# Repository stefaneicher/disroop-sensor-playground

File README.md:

# disroop-sensor-playground

**Ein kleiner Sensor-Würfel wird zum Gamecontroller:** Der Nordic Thingy:52 schickt seine Sensordaten per Bluetooth live an ein Dashboard. Er dient als Tennisschläger, und auf der Lauberhorn-Abfahrt lenkst du damit den Skifahrer.

> **Was ist der Thingy:52?** Ein etwa 6 × 6 cm grosses Entwicklungsboard von Nordic Semiconductor im Gummigehäuse. Es enthält einen nRF52832-Chip mit Bluetooth LE und NFC, eine Bewegungseinheit (Beschleunigung, Gyro, Kompass), Temperatur-, Feuchte- und Luftdrucksensor, Gas- und Farbsensor, Mikrofon, Lautsprecher, eine RGB-LED und einen Taster. Foto und Datenblatt: [Nordic Thingy:52 – Produktseite](https://www.nordicsemi.com/Products/Development-hardware/Nordic-Thingy-52), [Werksfirmware auf GitHub](https://github.com/NordicSemiconductor/Nordic-Thingy52-FW).

Das Projekt hat drei Teile. Der Thingy läuft dabei immer mit der **Werksfirmware**, Flashen ist nicht nötig.

### 1. Sensorübersicht mit Verwendungszwecken

Alle Sensorwerte laufen per Bluetooth LE live ins Terminal, in ein Web-Dashboard und in eine Android-App. Zu jedem Sensor erklärt das Dashboard, wofür man ihn braucht (ⓘ). Der Thingy spielt dazu „Highway to Hell“, die LED blinkt mit.

*Web-Dashboard im Simulator-Modus (`thingy.exe --sim`). Mobile-Ansicht: [docs/img/dashboard-mobile.png](docs/img/dashboard-mobile.png)*

*Android-App im Simulator-Modus. Die Bilder erzeugt `./project android screenshots`.*

### 2. Tennis

*Tennis im Browser, der Thingy ist der Schläger: `thingy.exe tennis` (live) oder `thingy.exe tennis --sim`. In der Android-App über „🎾 Tennis“. Mehr in [docs/TENNIS.md](docs/TENNIS.md).*

### 3. Skiabfahrt

*Abfahrt auf Lauberhorn und Streif, der Thingy ist der Lenker: kippen = lenken, Nase runter = Hocke, Ruck = Sprung. http://127.0.0.1:8052/ski oder in der Android-App über „⛷ Ski“. Mehr in [docs/SKI.md](docs/SKI.md).*

> **Thingy:52-Pfad: keine Firmware, kein Flashen, kein Debugger.** Für den Thingy wird keine eigene Firmware gebaut. Der Thingy läuft unverändert mit der Nordic-Werksfirmware (v2.x). Bridge und Android-App sind **BLE-Clients**:
> - **Empfangen:** Sie abonnieren die GATT-Notifications des Thingy (Sensordaten) und dekodieren sie.
> - **Senden:** Sie schreiben Befehle in GATT-Characteristics: Ton für das Lied, LED-Farbe, Sensor-Intervalle, NFC-Inhalt.
>
> Das hat Grenzen: Es geht nur, was die Werksfirmware anbietet. So ist z. B. die Mikrofon-Abtastrate fest auf 16 kHz. Deshalb ist die Lautstärkemessung standardmässig aus, sie würde die BLE-Verbindung überlasten.
>
> ```
> Thingy:52 (Werks-FW) ──BLE──▶ thingy.exe (Windows) ──▶ Terminal + Web-Dashboard :8052
>                      ──BLE──▶ Android-App ch.disroop.sensorplayground (direkt, Start per NFC)
> ```

Das separate Motion-One-Teilprojekt enthält dagegen eigene Firmwareentwürfe.

## Features

- **`thingy.exe`** (Go, Windows): verbindet sich per BLE mit dem Thingy und zeigt alle Werte live im Terminal:
  - Beschleunigung, Gyro, Kompass, Kurs, Euler-Winkel, Lage, Tippen, Schritte
  - Temperatur, Feuchte, Luftdruck, eCO₂/TVOC, Farbe
  - Mikrofonpegel, Taster, Akku, RSSI
- **Web-Dashboard** auf http://localhost:8052. Es ist in die exe eingebettet und bekommt die Daten live per Server-Sent Events. Es zeigt Charts, 3D-Lage und Kompass, und du kannst damit das Lied und die LED steuern.
- **Lied:** „Highway to Hell“ (Refrain, 24 Noten) über den Thingy-Lautsprecher. Die LED-Farbe folgt der Tonhöhe. Starten und stoppen geht per Taster am Thingy, im Dashboard oder in der App.
- **NFC:** `thingy.exe nfc` schreibt einen Android Application Record auf den NFC-Tag des Thingy. Hältst du das Handy an den Thingy, öffnet sich die App.
- **Android-App** `ch.disroop.sensorplayground`: verbindet sich direkt per BLE und zeigt dieselben Werte. Sie hat einen eingebauten Simulator.
- **Tennis** (`tennis/`, eigenes Programm): Tennis-Spiel mit three.js, der Thingy ist der Schläger. Schwung = Schlag, Neigen = laufen. Die Bridge liefert die Bewegung mit 100 Hz per WebSocket und spielt das Spiel unter `/tennis/` aus. Ohne Thingy mit Tastatur oder im Simulator spielbar. Dazu **Ski** (`tennis/src/ski/`): Lauberhorn und Streif in 3D, siehe [docs/SKI.md](docs/SKI.md).
- **Simulator** (`--sim`) für Demos, Tests und CI ohne Hardware.
- **Alles im Docker-Devcontainer:** Lokal wird ausser Docker nichts installiert.

## Quickstart

**Voraussetzungen**
- Windows 11 mit WSL2 (Ubuntu) und Docker in WSL
- Bluetooth-LE-Adapter unter Windows
- Thingy:52 mit Werksfirmware, geladen. Zum Aufwecken den Knopf drücken.

**Im Repo-Ordner unter WSL:**

```bash
./project image          # Devcontainer-Image bauen (einmalig, dauert einige Minuten)
./project build          # build/thingy.exe, build/thingy-linux, build/disroop-sensor-playground-debug.apk
./project bridge run     # thingy.exe auf Windows starten: Terminal-Live-Ansicht + Web-GUI
```

Dann im Browser http://localhost:8052 öffnen. `Strg+C` beendet die exe.

**Ohne Hardware:** `./project bridge run --sim` startet die exe mit dem Simulator.

**Tennis:** `./project play` (echter Thingy) oder `./project play --sim` baut alles, startet `thingy.exe tennis` und öffnet http://127.0.0.1:8052/tennis/. Mit dem Invoke-CLI: `./t tennis.play [--sim]`. Anleitung: [docs/TENNIS.md](docs/TENNIS.md).

> Die exe läuft über WSL-Interop **unter Windows**, weil WSL kein Bluetooth hat. Der Port lauscht nur auf `127.0.0.1` von Windows. Aus WSL brauchst du deshalb `curl.exe` statt `curl`, siehe [Troubleshooting](docs/TROUBLESHOOTING.md).

## Android-App installieren

1. APK bauen mit `./project android build`. Das ergibt `build/disroop-sensor-playground-debug.apk`. Ein GitHub-Release mit fertiger APK ist geplant, siehe [Releases](https://github.com/stefaneicher/disroop-sensor-playground/releases).
2. Installieren:
   - **Sideload:** APK aufs Handy kopieren, öffnen und „Unbekannte Apps installieren“ erlauben.
   - **adb (Windows):** `adb install -r build\disroop-sensor-playground-debug.apk`
3. Beim ersten Start die Berechtigung „Geräte in der Nähe“ (Bluetooth) erteilen.

Die APK ist mit einem öffentlich eingecheckten Demo-Schlüssel signiert. Neuinstallationen über lokale und CI-Builds hinweg funktionieren deshalb. Für den produktiven Einsatz ist sie nicht gedacht.

## NFC: Handy an den Thingy halten

```bash
./project bridge nfc             # Backup nach build/nfc-backup.hex, dann AAR "ch.disroop.sensorplayground" schreiben
./project bridge nfc --restore   # Original-Inhalt (Nordic-App) aus dem Backup zurückschreiben
```

Der Thingy nimmt nur **eine** BLE-Verbindung an. Während `nfc` läuft, müssen `thingy.exe` und die App getrennt sein.

## Projektstruktur

```
project                 CLI: ./project <befehl>, ruft scripts/<bereich>.sh auf
scripts/                bridge.sh, web.sh, tennis.sh, android.sh (Builds und Tests im Devcontainer)
.devcontainer/          Toolchain-Image (Go, Node, JDK 21, Android SDK, Chromium)
bridge/                 Go: thingy.exe (BLE, Decoder, Telemetrie, TUI, HTTP/SSE, Lied, NFC)
bridge/web/             Web-Dashboard (ES-Module ohne Build-Step), Tests, Mock-Server
tennis/                 Tennis: eigenes Spiel (TypeScript + three.js, kein Bundler), von der exe unter /tennis/ ausgeliefert
android/                Android-App (Kotlin, Compose) + reines Kotlin-Modul :protocol
shared/                 chorus.json (Lied), telemetry.example.json (Beispiel-Snapshot)
docs/                   Protokoll-Vertrag, Schema, Architektur, Anleitungen
devices/motion-one/     Eigener Controller „Disroop Motion One“: digitaler Entwurf, nicht hardwarevalidiert
build/                  Build-Ausgaben (nicht im Git)
```

## Motion One: aktueller Stand und Archiv

PCB/Firmware liegen auf r4; die Mechanikquellen enthalten r5-Änderungen, aber noch
keine gespeicherten r5-Prüfergebnisse. Verbindlich ist der
[Projektstand](devices/motion-one/management/PROJECT_STATE.md), visuell aufbereitet im
[aktuellen Überblick](devices/motion-one/media/presentation/index.html).
Die [V1-Baseline](devices/motion-one/releases/V1_BASELINE/VERIFIKATIONSMATRIX.md) und
der r3-Zwischenbericht bleiben historische Nachweise, keine aktuelle Fertigungsfreigabe.

Das [Dateiaudit](docs/DATEI_AUDIT.html) bewertet Projektpfade, Referenzhinweise und
bytegleiche Duplikate. Erneut erzeugen: `node scripts/audit-files.mjs`.
Fehlende Textreferenzen allein rechtfertigen keine Löschung.

Nach Veröffentlichung auf `main` direkt als HTML:
[Projektüberblick](https://raw.githack.com/stefaneicher/disroop-sensor-playground/main/devices/motion-one/media/presentation/index.html)
und [Dateiaudit](https://raw.githack.com/stefaneicher/disroop-sensor-playground/main/docs/DATEI_AUDIT.html).

## Dokumentation

Die Übersicht findest du in [docs/index.md](docs/index.md):

- [Architektur](docs/ARCHITECTURE.md)
- [Bedienung](docs/USAGE.md)
- [Entwicklung](docs/DEVELOPMENT.md)
- [Troubleshooting](docs/TROUBLESHOOTING.md)
- [Protokoll-Vertrag](docs/protocol.md)
- [Tennis](docs/TENNIS.md)
- READMEs der Bereiche: [bridge](bridge/README.md), [web](bridge/web/README.md), [tennis](tennis/README.md), [android](android/README.md)

## Lizenz

© 2026 Stefan Eicher. Alle Rechte vorbehalten, siehe [LICENSE](LICENSE). „Highway to Hell“ ist hier nur als grobe Tonfolge des Refrains enthalten (`shared/chorus.json`).

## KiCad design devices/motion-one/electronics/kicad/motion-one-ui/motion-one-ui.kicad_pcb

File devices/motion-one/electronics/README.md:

# Elektronik und PCB

Hier liegen Schaltplan, KiCad-Layout, elektrische Simulationen, Baugruppenexport und Firmware-Pinout.

## Stand

Standabgleich 2026-11-13: PCB r4 mit integriertem hierarchischem Schaltplan r4-C.
Die gespeicherten Integrationsbelege vom 2026-11-09 melden Netzlisten MATCH, ERC
ohne Fehler und keine offenen Verbindungen; Hauptplatine mit zwei DRC-Warnungen,
UI ohne DRC-Warnungen [QUELLE:
`exports/pruefbelege_schaltplan_r4/hierarchy-integration.json`]. Die UI-Platine ist
optional und nicht Teil des Geräts/Gehäuses r4. Gesamtstatus **PARTIAL**;
verbindlich ist [PROJECT_STATE](../management/PROJECT_STATE.md).

Das V1-Board ist als 4-Lagen-KiCad-Projekt (70 × 25 × 1,0 mm) erstellt und vollständig geroutet. Der dokumentierte
Prüflauf meldet ERC: 0 Fehler und DRC: 0 Fehler/0 unverbundene Netze; zwei USB-C-Silkscreen-Warnungen sind begründet.
SPICE-Fälle für Power-Path, Einschaltstrom, Summer/Motor und Akku-Messteiler wurden simuliert.

*KiCad-Render des digitalen PCB-Entwurfs, keine gefertigte Platine. Die endgültige PCB-/Gehäuse-Abstimmung läuft noch.*

Diese Ergebnisse gelten für den prototypischen Entwurf, nicht für ein gefertigtes Board. Der PCB-/Gehäuse-Abgleich und
die finale Revision laufen; die Fertigungsdaten müssen nach Änderungen neu exportiert und geprüft werden.

## Wichtige Dateien

- `kicad/motion-one/`: `.kicad_sch`, `.kicad_pcb`, lokale Bibliotheken und STEP-Export
- `analysis/ANALYSE_V1.md`: Leistungs-, Lade-, Regler-, Toleranz- und Fertigungsanalyse
- `spice/`: ngspice-Netzlisten, Logs und Ergebnisse
- `PINOUT_V1.json`: Sollbelegung der E73-Modulsignale; wird vom Firmware-Board-Overlay übernommen
- `../manufacturing/pcba/`: Gerber, Bohrdaten, JLC-BOM/CPL und Renderings
- `../sourcing/BOM_V1.md`: Bauteile, Teilenummern und Lager-Snapshots

## Schnittstellen / offene Punkte

`../management/INTERFACES.json` ist der gemeinsame Vertrag zu Boardumriss, Bauhöhen und Positionen. Der aktuelle
PCB-Stand braucht noch die fachübergreifende Abstimmung mit der Mechanik, anschliessend neue ERC/DRC- und
Fertigungsexporte. CPL-Rotationen sind in der Bestückervorschau zu bestätigen. Finale PCBA- und Versandpreise sind
nicht belegt; ohne Bestellung/Muster bleiben elektrische Messungen NOT RUN.

## Reproduktion

Werkzeuge ausschliesslich im Hardware-Image ausführen, zum Beispiel:

```sh
./project hw run "kicad-cli version"
./project hw run "ngspice -b devices/motion-one/electronics/spice/powerpath.cir"
```

Der aktuelle Hauptschaltplan-Generator ist `../scripts/electronics/gen_mo_sch_hier.py`.
Ältere Generatoren und Migrationsskripte sind keine austauschbaren Einstiegspunkte:
Sie können ältere Stände erzeugen oder Quellen verändern. Die genauen Generator-,
ERC-, DRC- und Exportbefehle stehen in `../scripts/electronics/` und im datierten PCB-Handoff.

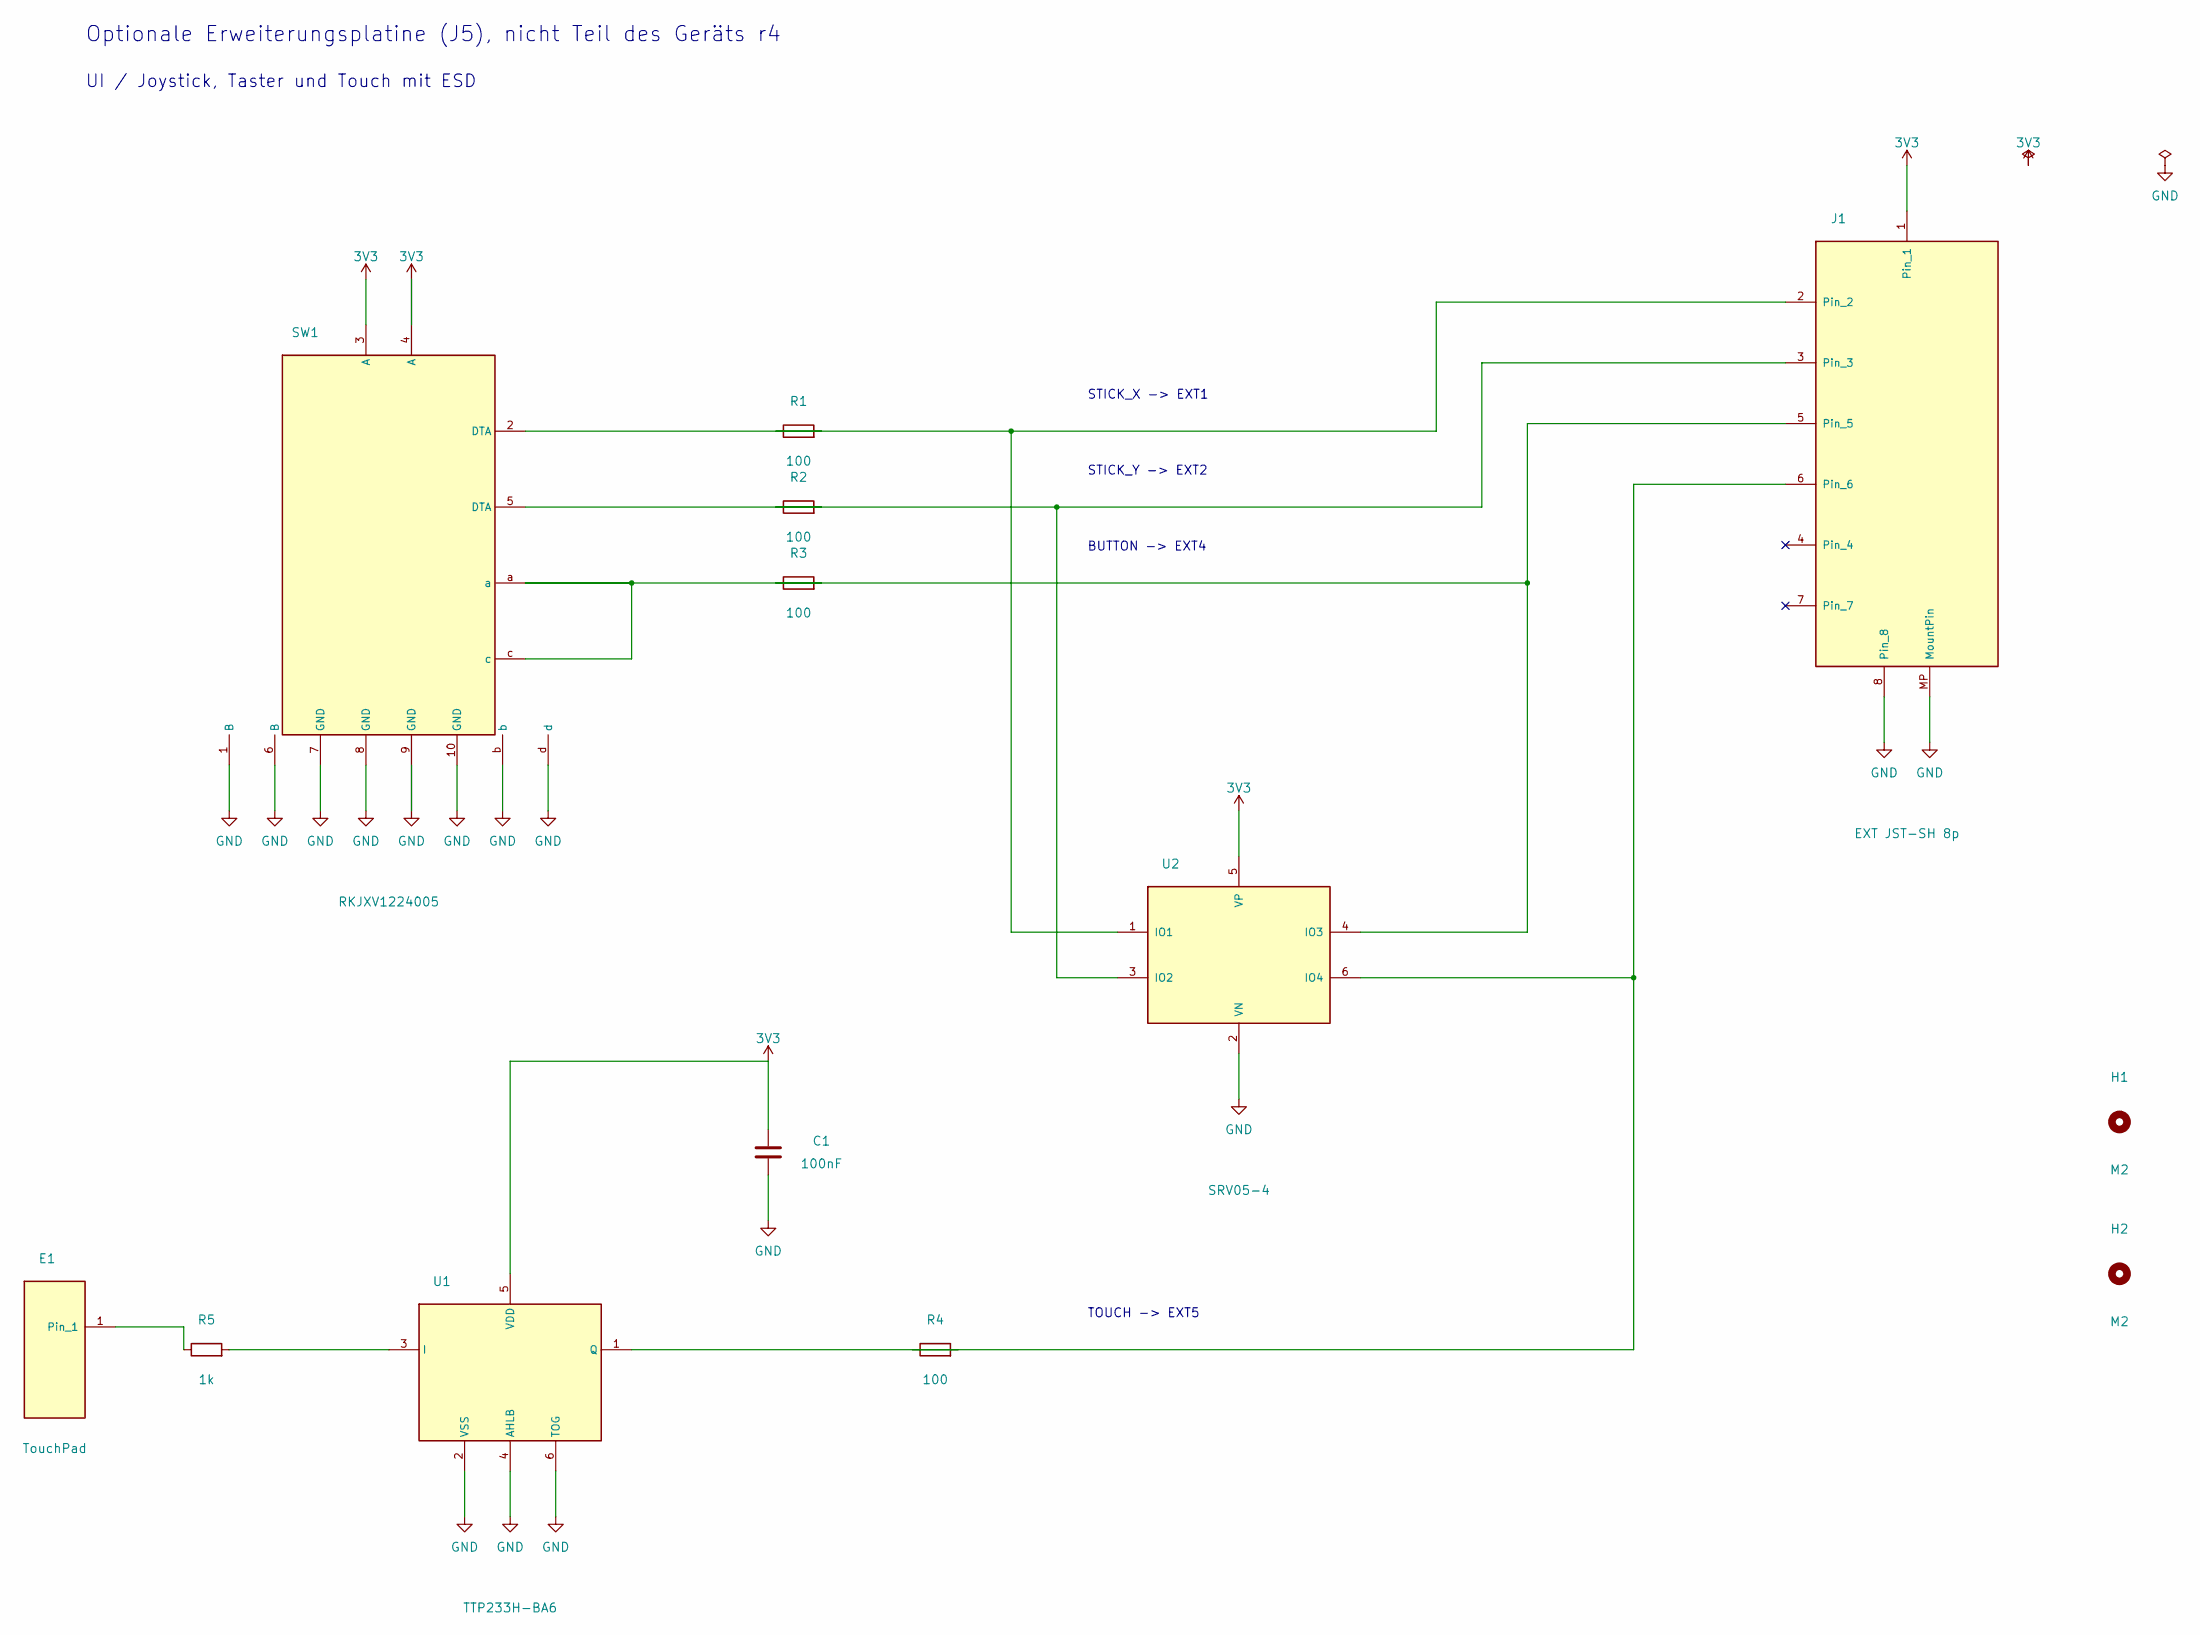
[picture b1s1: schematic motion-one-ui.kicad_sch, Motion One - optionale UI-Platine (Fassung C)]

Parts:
C1: 100nF; C_0402_1005Metric; LCSC C1525
E1: TouchPad; TouchPad_10x10
H1, H2: M2; MountingHole_2.2mm_M2
J1: EXT JST-SH 8p; JST_SH_SM08B-SRSS-TB_1x08-1MP_P1.00mm_Horizontal; LCSC C160407
R1, R2, R3, R4: 100; R_0402_1005Metric; LCSC C25076
R5: 1k; R_0402_1005Metric; LCSC C11702
SW1: RKJXV1224005; SW-TH_RKJXV1224005; MPN RKJXV1224005; LCSC Part C146170
U1: TTP233H-BA6; SOT-23-6_L2.9-W1.7-P0.95-LS2.8-BL; MPN TTP233H-BA6; LCSC Part C2890349
U2: SRV05-4; SOT-23-6; LCSC C13612

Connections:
3V3: C1.1, J1.1, SW1.3 (A), SW1.4 (A), U1.5 (VDD), U2.5 (VP)
GND: C1.2, J1.8, J1.MP (MountPin), SW1.1 (B), SW1.6 (B), SW1.7 (GND), SW1.8 (GND), SW1.9 (GND), SW1.10 (GND), SW1.b, SW1.d, U1.2 (VSS), U1.4 (AHLB), U1.6 (TOG), U2.2 (VN)
unnamed: E1.1, R5.1
unnamed: J1.2, R1.1, U2.1 (IO1)
unnamed: J1.3, R2.1, U2.3 (IO2)
unnamed: J1.5, R3.1, U2.4 (IO3)
unnamed: J1.6, R4.1, U2.6 (IO4)
unnamed: R1.2, SW1.2 (DTA)
unnamed: R2.2, SW1.5 (DTA)
unnamed: R3.2, SW1.a, SW1.c
unnamed: R5.2, U1.3 (I)
unnamed: R4.2, U1.1 (Q)

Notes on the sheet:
Optionale Erweiterungsplatine (J5), nicht Teil des Geräts r4
UI / Joystick, Taster und Touch mit ESD
STICK_X -> EXT1
STICK_Y -> EXT2
BUTTON -> EXT4
TOUCH -> EXT5

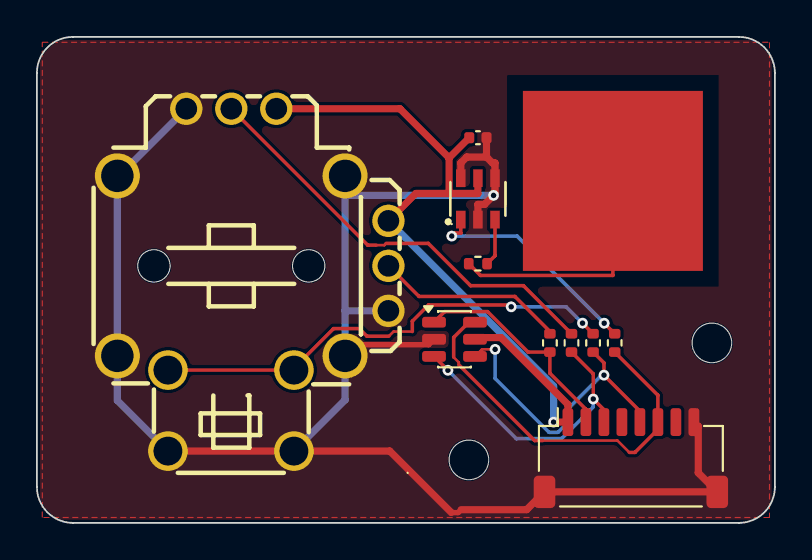
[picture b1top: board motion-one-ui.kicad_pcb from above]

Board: 2 copper layers, 41.0 x 27.0 mm, 13 parts (0 on the bottom side), 12 nets.

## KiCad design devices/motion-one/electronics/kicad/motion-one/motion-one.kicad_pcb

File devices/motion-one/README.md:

# Disroop Motion One

Ein geplanter Einhand-Motion-Controller für Tennis und Ski. Das Gerät soll das Thingy:52-BLE-Profil nachbilden, damit
Bridge, Spiele und Android-App ohne Codeänderungen funktionieren.

> **Aktueller Überblick:** [Projektstand mit Prüfgrenzen und Archiv](media/presentation/index.html).
> Verbindliche Statusquelle: [PROJECT_STATE.md](management/PROJECT_STATE.md), Abgleich vom 2026-11-13.

## Aktueller Stand

V1 ist ein **digitaler Entwicklungsstand**, noch kein fertiges oder geprüftes Produkt: PCB, Firmware und ergonomisches
Gehäuse liegen als Entwürfe vor. Die Gesamtintegration ist noch offen. Nach letztem dokumentiertem Stand wurde nichts bestellt, bezahlt,
gedruckt, geflasht oder unter Spannung gesetzt; ein neuer Durchführungsnachweis fehlt, Hardwaretests sind NOT RUN. Der detaillierte Status und die nächsten
Schritte stehen im [verbindlichen Projektstand](management/PROJECT_STATE.md).
PCB/Firmware: r4; Mechanikquellen: r5, gespeicherte Mechanik-Prüfbelege: r4.
Die V1-Baseline ist ein historischer Snapshot, keine r5-Fertigungsfreigabe.

## Themen

| Bereich | Kurzfassung | Status |
|---|---|---|
| [Elektronik / PCB](electronics/README.md) | KiCad-Board, Schaltplan, SPICE-Analyse und Pinout | Entwurf; finale Mechanik-Abstimmung offen |
| [Firmware](firmware/README.md) | Zephyr-Firmware mit Thingy-Profil, Bewegungserfassung und UF2-Programmierweg | 69 Tests ohne Fehler und Pinchecks im gespeicherten r4-Log [QUELLE: logs/fw-pinmap/unit-tests.log]; Hardware NOT RUN |
| [Mechanik](mechanics/README.md) | Parametrisches, beidhändig nutzbares Griffgehäuse, FEM und 3D-Druck | CAD und Slicer-Daten vorhanden; PCB-Abgleich offen |
| [Fertigung](manufacturing/README.md) | PCBA-Uploadpaket und Slicer-Ausgaben | Dateien vorbereitet; noch kein Auftrag oder Druck |
| [Beschaffung](sourcing/README.md) | BOM, Lagerabfragen und Bestücker-Vergleich | Momentaufnahme; finale Versand- und PCBA-Angebote offen |

## Projektdateien

- [Entwicklungsprompt](PROMPT_1_ENTWICKLUNG.md) und [Marktauftritt-Prompt](PROMPT_2_MARKTAUFTRITT.md)
- [Aktueller Projektüberblick](media/presentation/index.html)
- [Archiv: Zwischenbericht r3 vom 2026-11-08](media/presentation/ZWISCHENBERICHT_2026-11-08_r3.html)
- [Dateiaudit und Aufräumkandidaten](../../docs/DATEI_AUDIT.html)
- [Vorab-Check](PREFLIGHT.md) und [Vorbildanalyse](ANALYSE.md)
- [Hauptprotokoll](../../docs/protocol.md)

Alle Masse, Preise und Leistungswerte sind Quellenangaben, Berechnungen, Simulationen oder Annahmen; Details und
Belegpfade stehen in den jeweiligen Bereichs-README-Dateien und Handoffs. CE/RED, FCC, UN38.3, EMV und physische
Sicherheit sind nicht validiert.

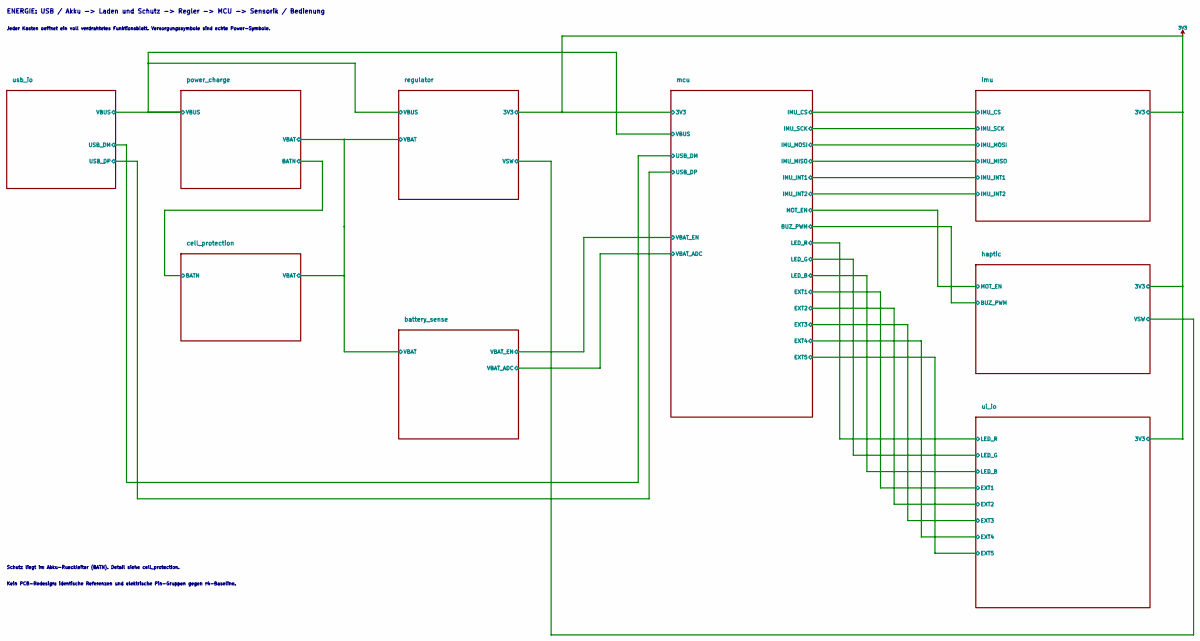
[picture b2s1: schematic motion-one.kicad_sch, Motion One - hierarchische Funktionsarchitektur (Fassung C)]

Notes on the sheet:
ENERGIE: USB / Akku -> Laden und Schutz -> Regler -> MCU -> Sensorik / Bedienung
Jeder Kasten oeffnet ein voll verdrahtetes Funktionsblatt. Versorgungssymbole sind echte Power-Symbole.
Schutz liegt im Akku-Rueckleiter (BATN). Detail siehe cell_protection.
Kein PCB-Redesign: identische Referenzen und elektrische Pin-Gruppen gegen r4-Baseline.

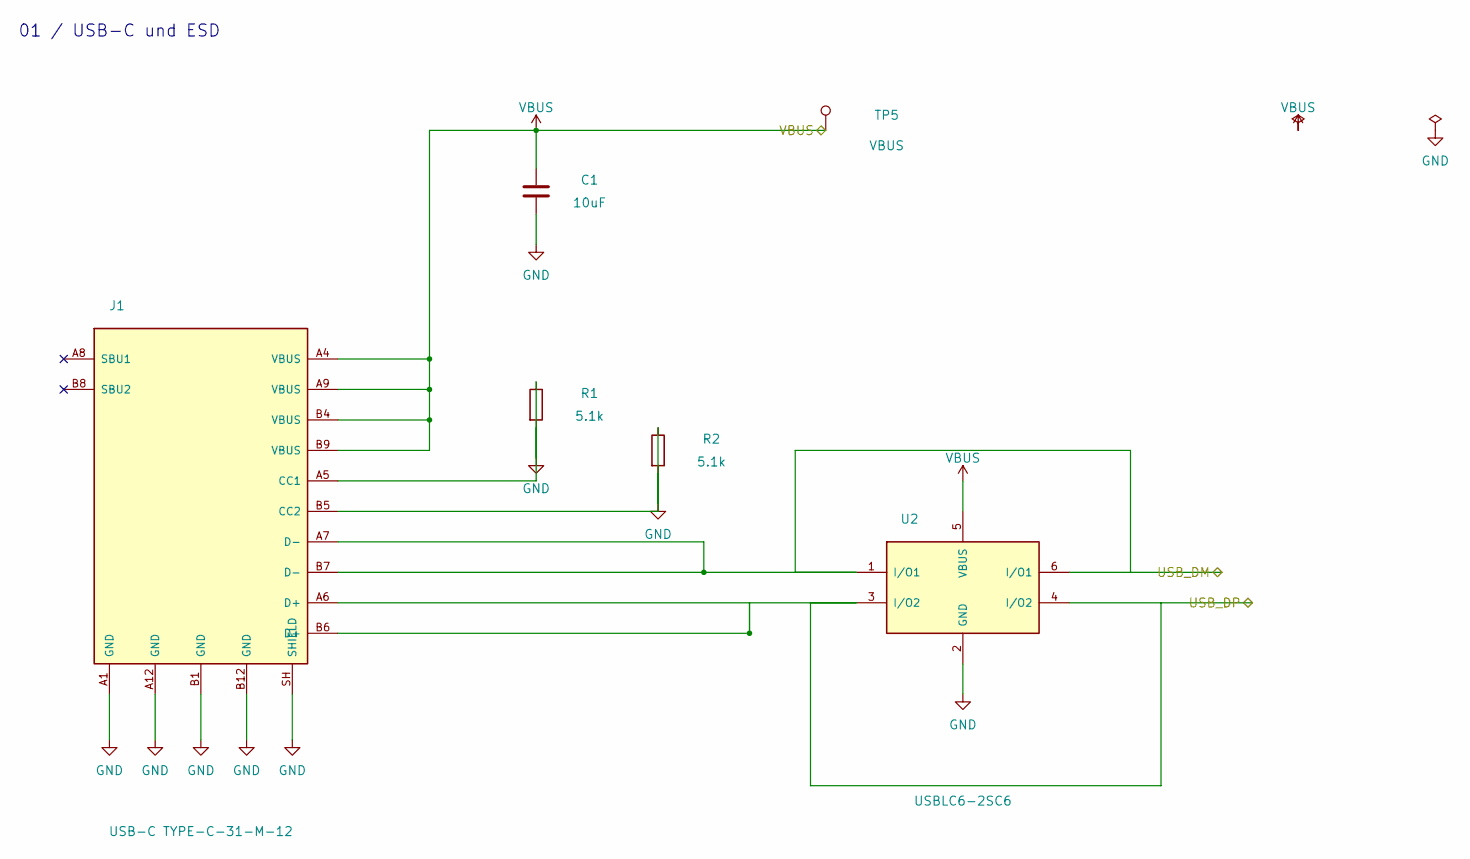
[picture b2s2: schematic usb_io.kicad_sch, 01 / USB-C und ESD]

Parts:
C1: 10uF; C_0805_2012Metric; LCSC C15850
J1: USB-C TYPE-C-31-M-12; USB_C_Receptacle_HRO_TYPE-C-31-M-12; LCSC C165948
R1, R2: 5.1k; R_0402_1005Metric; LCSC C25905
TP5: VBUS; TestPoint_Pad_D1.0mm
U2: USBLC6-2SC6; SOT-23-6; LCSC C7519

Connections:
/mcu/USB_DM: J1.A7 (D-), J1.B7 (D-), U2.1 (I/O1), U2.6 (I/O1); also elsewhere on the board
/mcu/USB_DP: J1.A6 (D+), J1.B6 (D+), U2.3 (I/O2), U2.4 (I/O2); also elsewhere on the board
VBUS: C1.1, J1.A4 (VBUS), J1.A9 (VBUS), J1.B4 (VBUS), J1.B9 (VBUS), TP5.1, U2.5 (VBUS); also elsewhere on the board

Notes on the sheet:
01 / USB-C und ESD

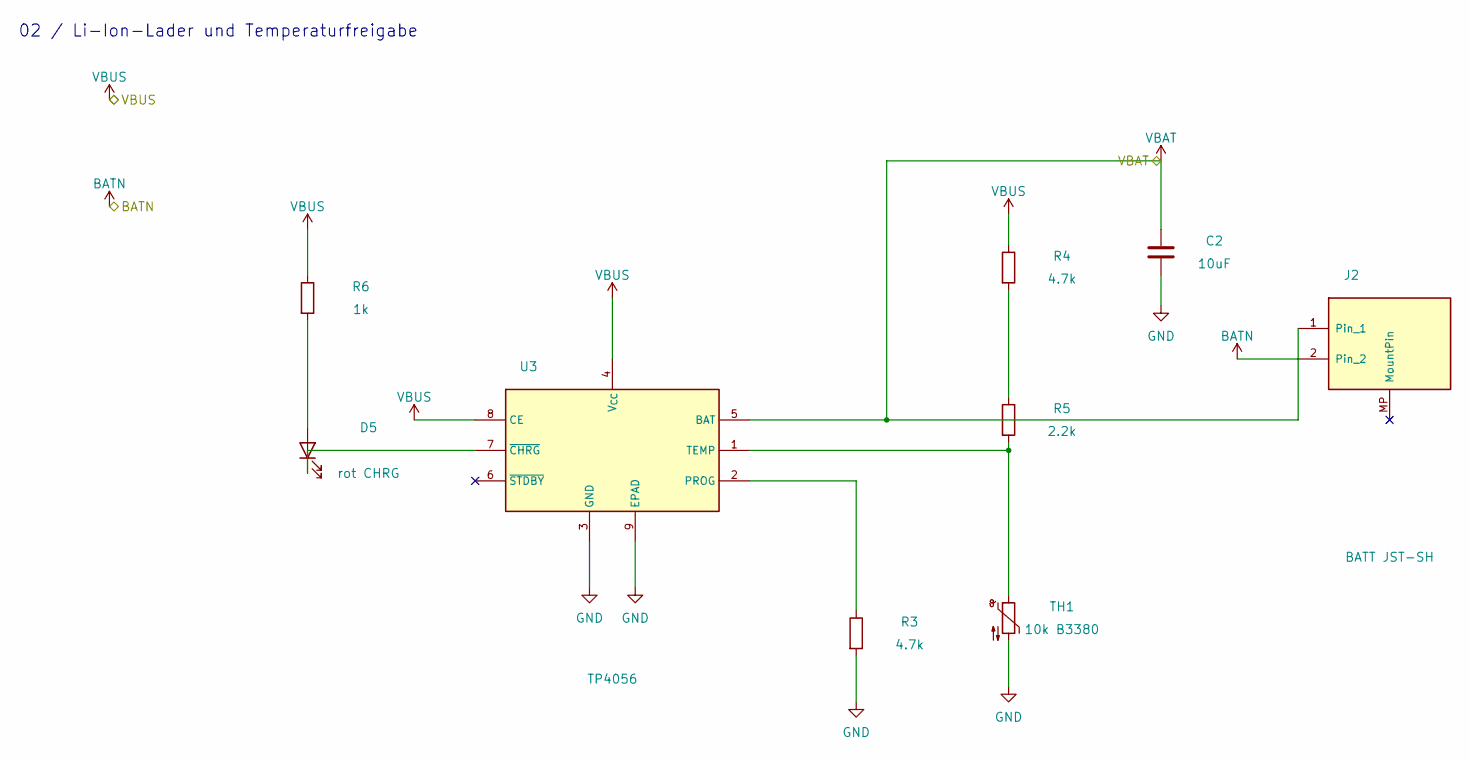
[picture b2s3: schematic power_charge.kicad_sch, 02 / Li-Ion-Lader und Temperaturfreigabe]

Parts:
C2: 10uF; C_0805_2012Metric; LCSC C15850
D5: rot CHRG; LED_0603_1608Metric; LCSC C2286
J2: BATT JST-SH; JST_SH_SM02B-SRSS-TB_1x02-1MP_P1.00mm_Horizontal; LCSC C160402
R3, R4: 4.7k; R_0402_1005Metric; LCSC C25900
R5: 2.2k; R_0402_1005Metric; LCSC C25879
R6: 1k; R_0402_1005Metric; LCSC C11702
TH1: 10k B3380; R_0402_1005Metric; LCSC C77131
U3: TP4056; SOIC-8-1EP_3.9x4.9mm_P1.27mm_EP2.29x3mm; LCSC C16581

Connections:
unnamed: D5.2 (A), R6.2
unnamed: D5.1 (K), U3.7 (~CHRG)
unnamed: R4.2, R5.1
unnamed: R3.1, U3.2 (PROG)
unnamed: R5.2, TH1.1, U3.1 (TEMP)
VBAT: C2.1, J2.1, U3.5 (BAT); also elsewhere on the board
VBUS: R4.1, R6.1, U3.4 (V_{CC}), U3.8 (CE); also elsewhere on the board

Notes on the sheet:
02 / Li-Ion-Lader und Temperaturfreigabe

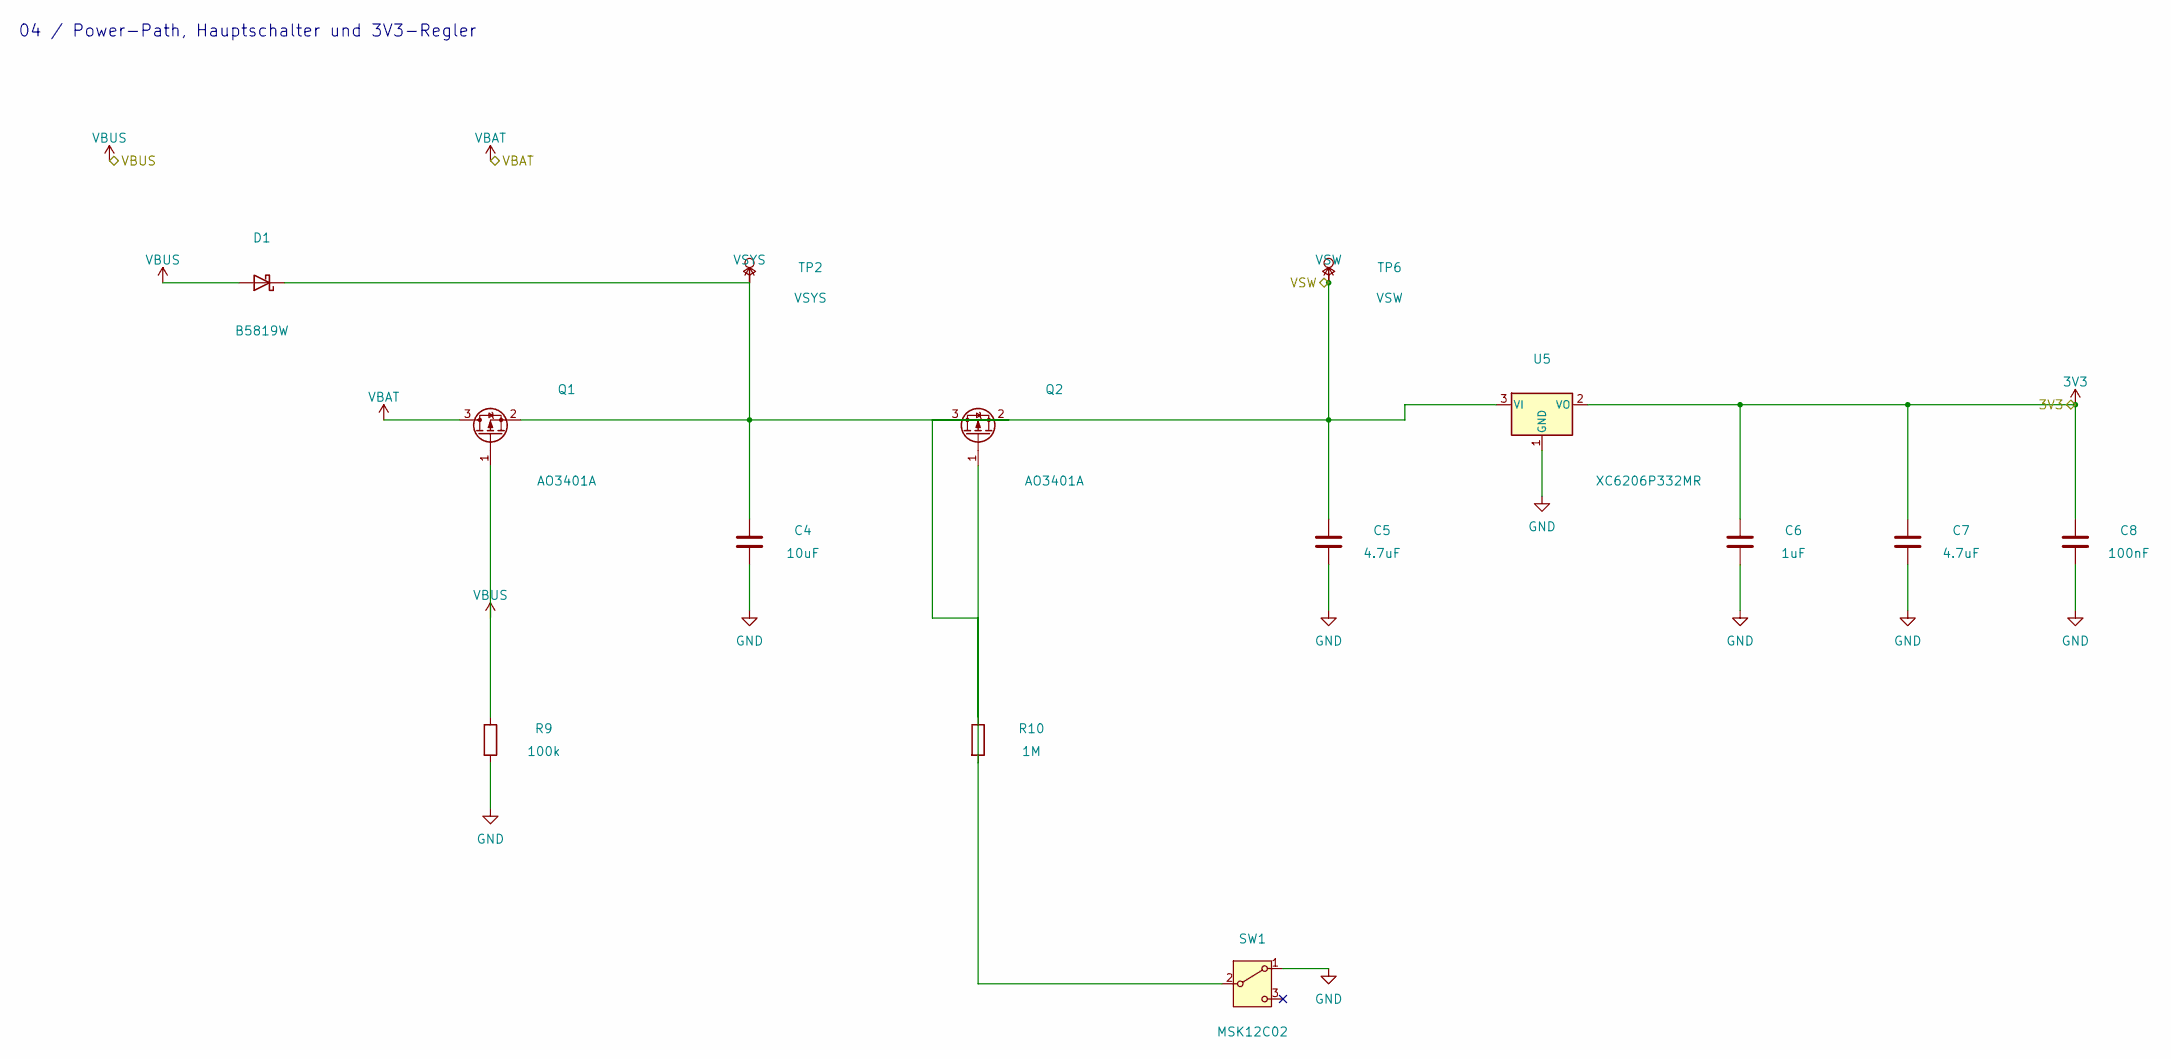
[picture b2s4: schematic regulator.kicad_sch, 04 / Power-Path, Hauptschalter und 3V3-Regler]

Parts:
C4: 10uF; C_0805_2012Metric; LCSC C15850
C5, C7: 4.7uF; C_0603_1608Metric; LCSC C19666
C6: 1uF; C_0402_1005Metric; LCSC C52923
C8: 100nF; C_0402_1005Metric; LCSC C1525
D1: B5819W; D_SOD-123; LCSC C8598
Q1, Q2: AO3401A; SOT-23-3; LCSC C15127
R9: 100k; R_0402_1005Metric; LCSC C25741
R10: 1M; R_0402_1005Metric; LCSC C26083
SW1: MSK12C02; SW_SPDT_Shouhan_MSK12C02; LCSC C431540
TP2: VSYS; TestPoint_Pad_D1.0mm
TP6: VSW; TestPoint_Pad_D1.0mm
U5: XC6206P332MR; SOT-23-3; LCSC C5446

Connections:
3V3: C6.1, C7.1, C8.1, U5.2 (VO); also elsewhere on the board
unnamed: Q2.1 (G), R10.2, SW1.2 (B)
VBAT: Q1.3 (D); also elsewhere on the board
VBUS: D1.2 (A), Q1.1 (G), R9.1; also elsewhere on the board
VSW: C5.1, Q2.3 (D), TP6.1, U5.3 (VI); also elsewhere on the board
VSYS: C4.1, D1.1 (K), Q1.2 (S), Q2.2 (S), R10.1, TP2.1

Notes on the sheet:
04 / Power-Path, Hauptschalter und 3V3-Regler

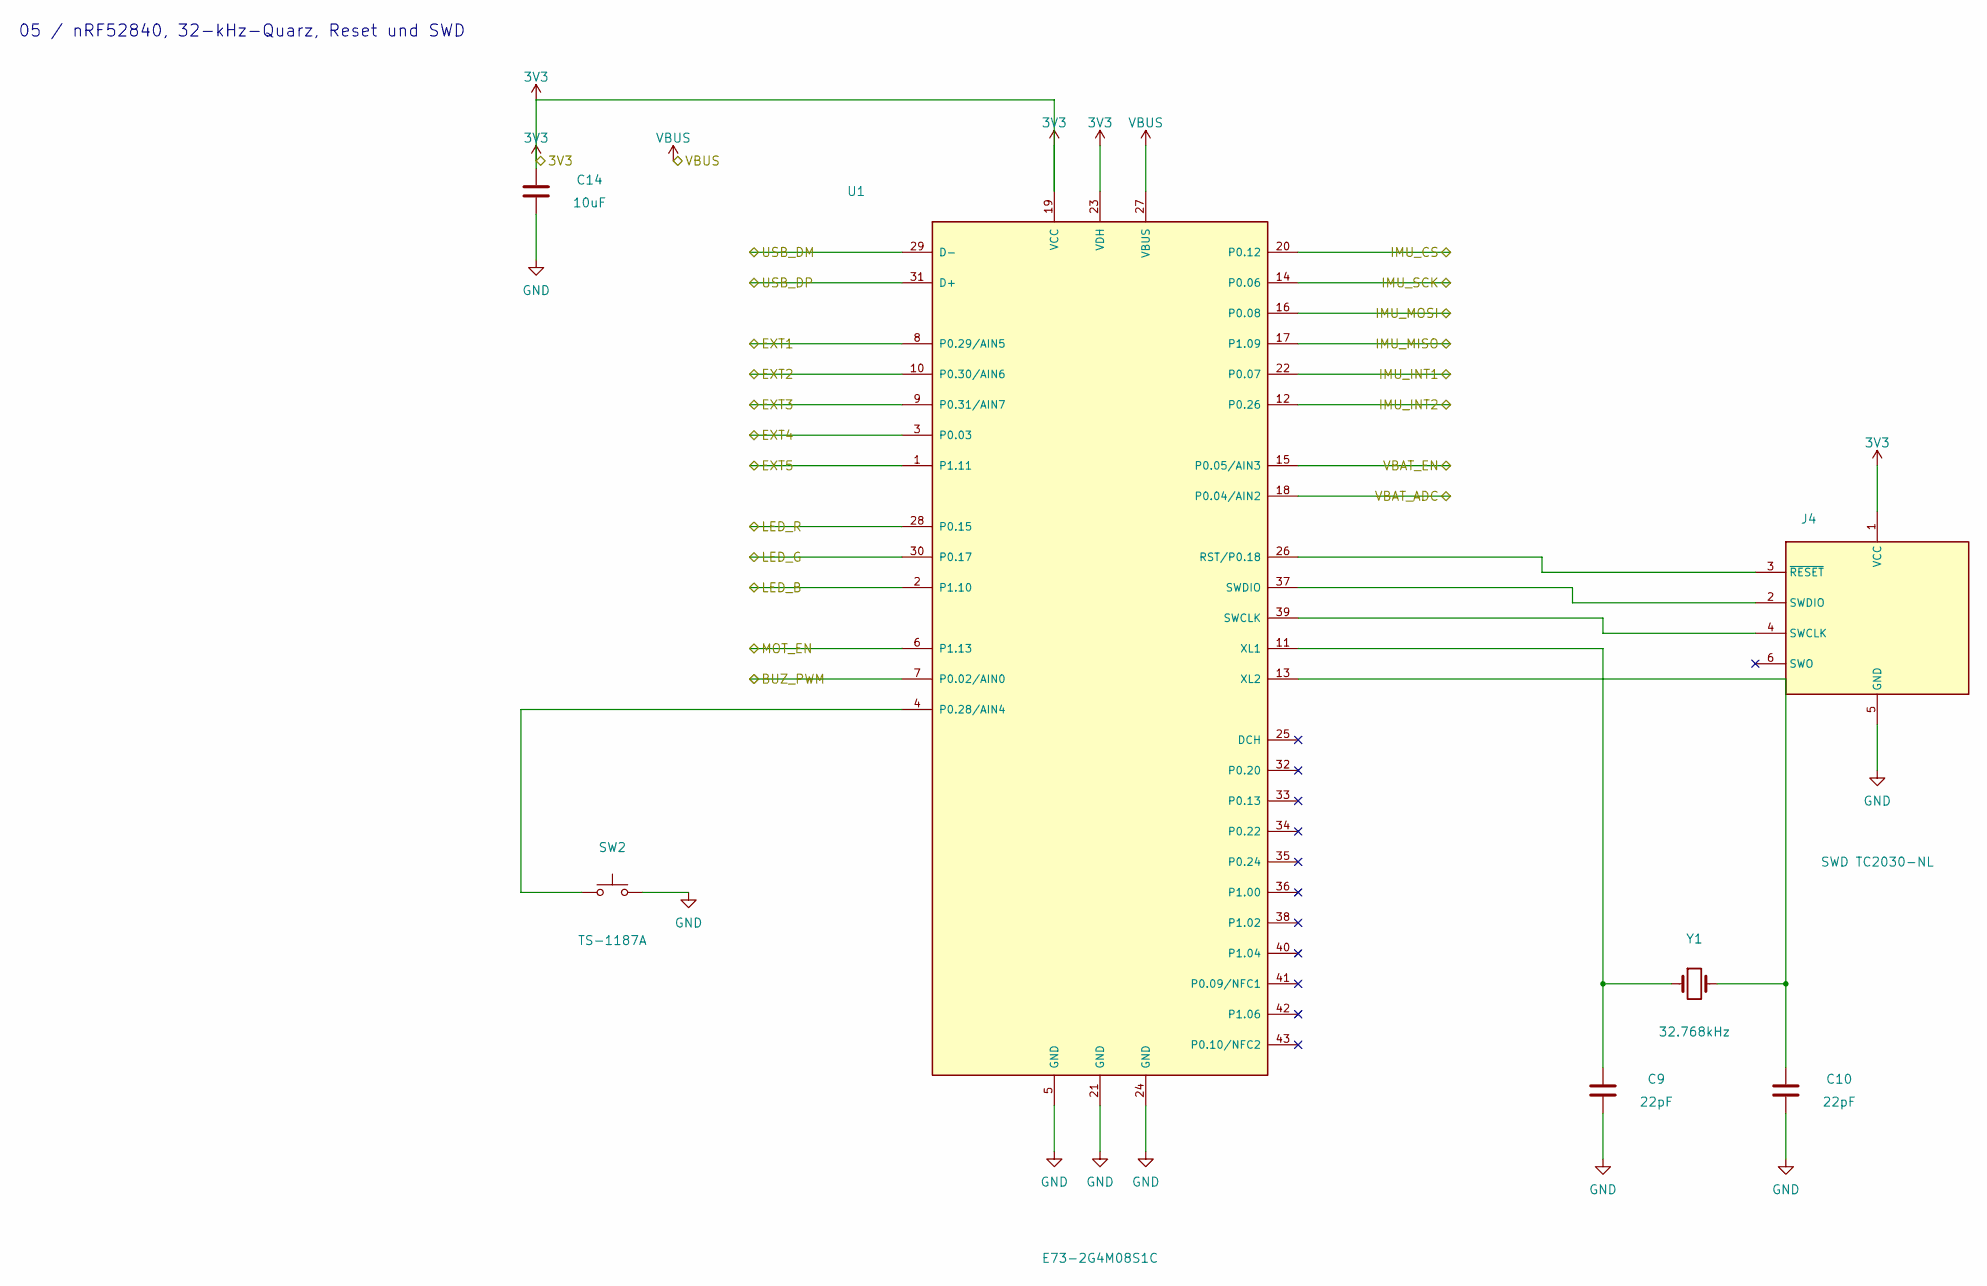
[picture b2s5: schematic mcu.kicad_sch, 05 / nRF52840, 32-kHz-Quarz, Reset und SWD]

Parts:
C9, C10: 22pF; C_0402_1005Metric; LCSC C1555
C14: 10uF; C_0805_2012Metric; LCSC C15850
J4: SWD TC2030-NL; Tag-Connect_TC2030-IDC-NL_2x03_P1.27mm_Vertical
SW2: TS-1187A; SW_Push_1P1T_XKB_TS-1187A; LCSC C318884
U1: E73-2G4M08S1C; LCSC C356849
Y1: 32.768kHz; Crystal_SMD_3215-2Pin_3.2x1.5mm; LCSC C32346

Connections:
3V3: C14.1, J4.1 (VCC), U1.19 (VCC), U1.23 (VDH); also elsewhere on the board
/battery_sense/VBAT_ADC: U1.18 (P0.04/AIN2); also elsewhere on the board
/battery_sense/VBAT_EN: U1.15 (P0.05/AIN3); also elsewhere on the board
/haptic/BUZ_PWM: U1.7 (P0.02/AIN0); also elsewhere on the board
/haptic/MOT_EN: U1.6 (P1.13); also elsewhere on the board
/imu/IMU_CS: U1.20 (P0.12); also elsewhere on the board
/imu/IMU_INT1: U1.22 (P0.07); also elsewhere on the board
/imu/IMU_INT2: U1.12 (P0.26); also elsewhere on the board
/imu/IMU_MISO: U1.17 (P1.09); also elsewhere on the board
/imu/IMU_MOSI: U1.16 (P0.08); also elsewhere on the board
/imu/IMU_SCK: U1.14 (P0.06); also elsewhere on the board
/mcu/EXT1: U1.8 (P0.29/AIN5); also elsewhere on the board
/mcu/EXT2: U1.10 (P0.30/AIN6); also elsewhere on the board
/mcu/EXT3: U1.9 (P0.31/AIN7); also elsewhere on the board
/mcu/EXT4: U1.3 (P0.03); also elsewhere on the board
/mcu/EXT5: U1.1 (P1.11); also elsewhere on the board
/mcu/LED_B: U1.2 (P1.10); also elsewhere on the board
/mcu/LED_G: U1.30 (P0.17); also elsewhere on the board
/mcu/LED_R: U1.28 (P0.15); also elsewhere on the board
/mcu/USB_DM: U1.29 (D-); also elsewhere on the board
/mcu/USB_DP: U1.31 (D+); also elsewhere on the board
unnamed: J4.4 (SWCLK), U1.39 (SWCLK)
unnamed: J4.2 (SWDIO), U1.37 (SWDIO)
unnamed: J4.3 (~RESET), U1.26 (RST/P0.18)
unnamed: SW2.1, U1.4 (P0.28/AIN4)
unnamed: C9.1, U1.11 (XL1), Y1.1
unnamed: C10.1, U1.13 (XL2), Y1.2
VBUS: U1.27 (VBUS); also elsewhere on the board

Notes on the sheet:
05 / nRF52840, 32-kHz-Quarz, Reset und SWD

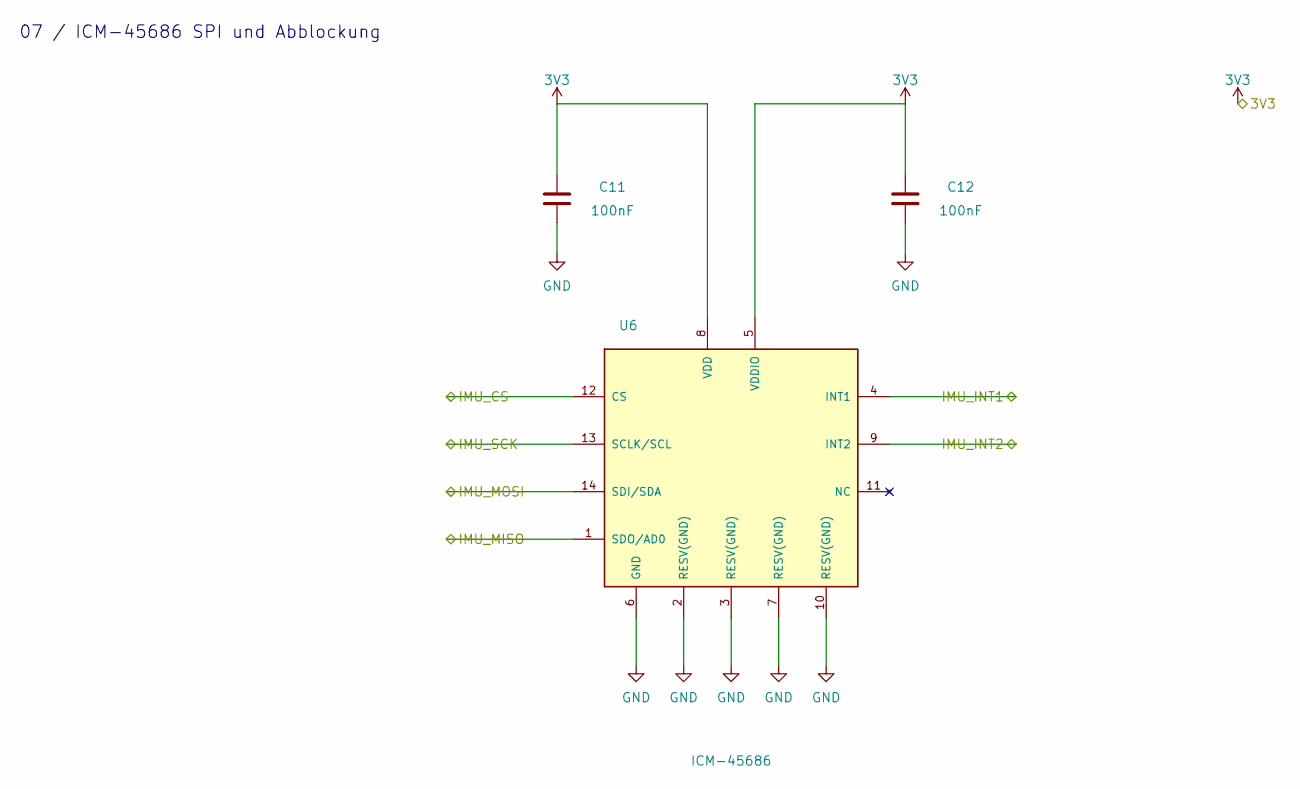
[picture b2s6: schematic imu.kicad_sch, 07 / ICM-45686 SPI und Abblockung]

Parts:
C11, C12: 100nF; C_0402_1005Metric; LCSC C1525
U6: ICM-45686; LGA-14_3x2.5mm_P0.5mm_LayoutBorder3x4y; LCSC C22459454

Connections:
3V3: C11.1, C12.1, U6.5 (VDDIO), U6.8 (VDD); also elsewhere on the board
/imu/IMU_CS: U6.12 (CS); also elsewhere on the board
/imu/IMU_INT1: U6.4 (INT1); also elsewhere on the board
/imu/IMU_INT2: U6.9 (INT2); also elsewhere on the board
/imu/IMU_MISO: U6.1 (SDO/AD0); also elsewhere on the board
/imu/IMU_MOSI: U6.14 (SDI/SDA); also elsewhere on the board
/imu/IMU_SCK: U6.13 (SCLK/SCL); also elsewhere on the board

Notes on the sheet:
07 / ICM-45686 SPI und Abblockung
